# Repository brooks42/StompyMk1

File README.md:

# StompyMk1
A small quadruped robot made of 9g servos and hope.

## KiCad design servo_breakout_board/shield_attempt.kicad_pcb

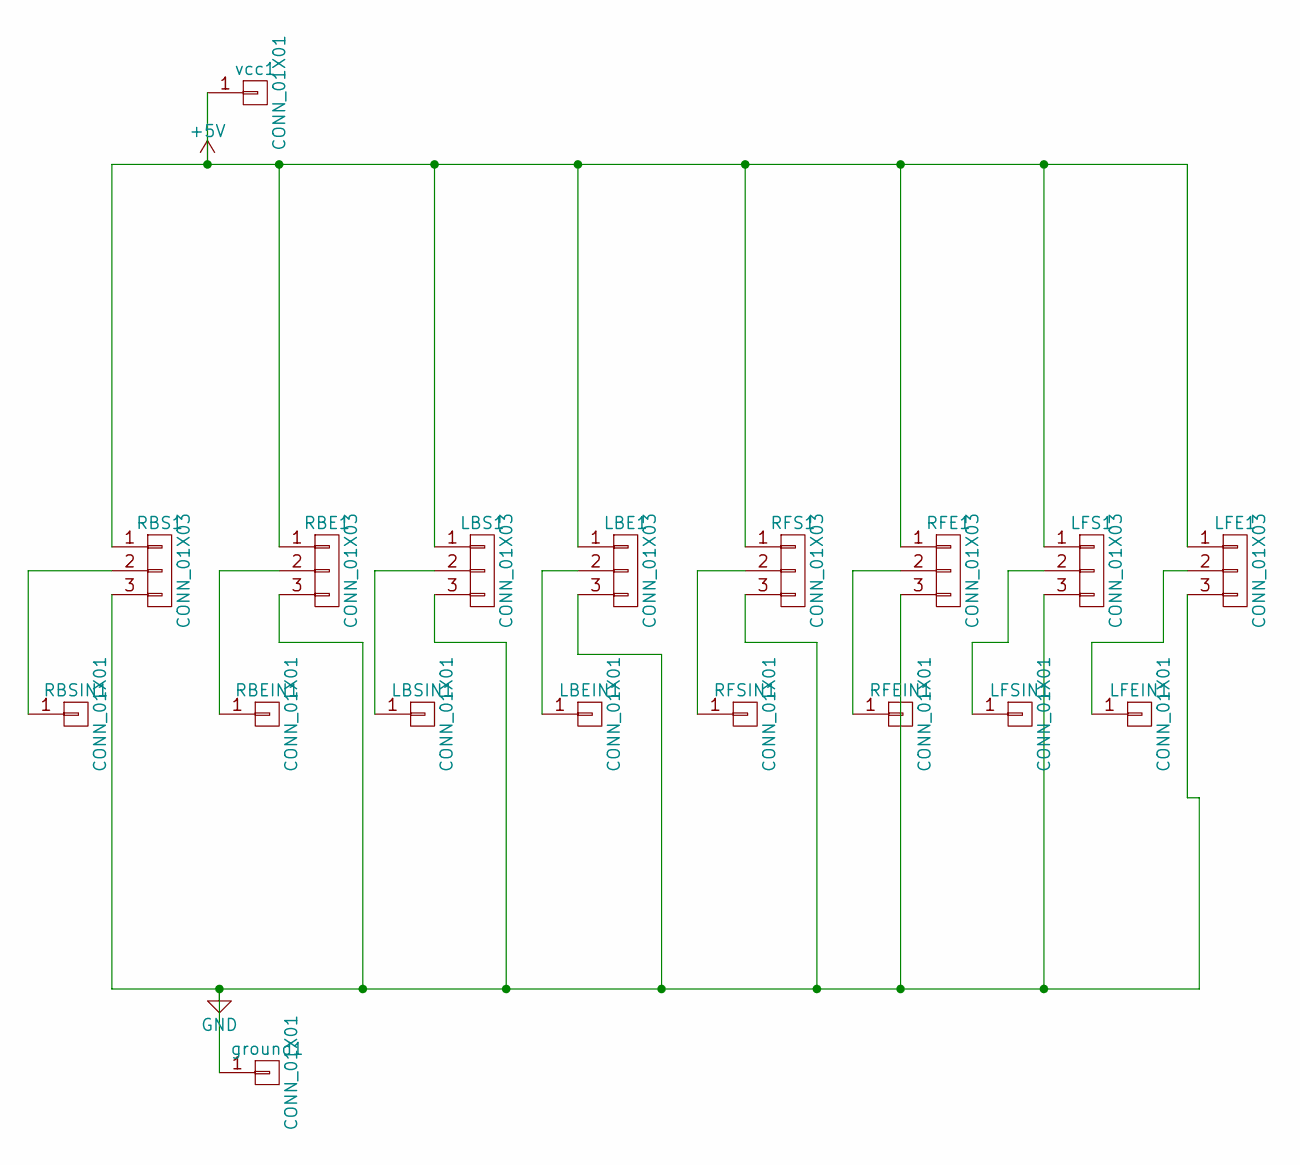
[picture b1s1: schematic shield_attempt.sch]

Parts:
LBE1: CONN_01X03; Pin_Header_Straight_1x03
LBEIN1: CONN_01X01; Pin_Header_Straight_1x01
LBS1: CONN_01X03; Pin_Header_Straight_1x03
LBSIN1: CONN_01X01; Pin_Header_Straight_1x01
LFE1: CONN_01X03; Pin_Header_Straight_1x03
LFEIN1: CONN_01X01; Pin_Header_Straight_1x01
LFS1: CONN_01X03; Pin_Header_Straight_1x03
LFSIN1: CONN_01X01; Pin_Header_Straight_1x01
RBE1: CONN_01X03; Pin_Header_Straight_1x03
RBEIN1: CONN_01X01; Pin_Header_Straight_1x01
RBS1: CONN_01X03; Pin_Header_Straight_1x03
RBSIN1: CONN_01X01; Pin_Header_Straight_1x01
RFE1: CONN_01X03; Pin_Header_Straight_1x03
RFEIN1: CONN_01X01; Pin_Header_Straight_1x01
RFS1: CONN_01X03; Pin_Header_Straight_1x03
RFSIN1: CONN_01X01; Pin_Header_Straight_1x01
ground1: CONN_01X01; Pin_Header_Straight_1x01
vcc1: CONN_01X01; Pin_Header_Straight_1x01

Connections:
+5V: LBE1.1, LBS1.1, LFE1.1, LFS1.1, RBE1.1, RBS1.1, RFE1.1, RFS1.1, vcc1.1
GND: LBE1.3, LBS1.3, LFE1.3, LFS1.3, RBE1.3, RBS1.3, RFE1.3, RFS1.3, ground1.1
unnamed: LBE1.2, LBEIN1.1
unnamed: LBS1.2, LBSIN1.1
unnamed: LFE1.2, LFEIN1.1
unnamed: LFS1.2, LFSIN1.1
unnamed: RBE1.2, RBEIN1.1
unnamed: RBS1.2, RBSIN1.1
unnamed: RFE1.2, RFEIN1.1
unnamed: RFS1.2, RFSIN1.1

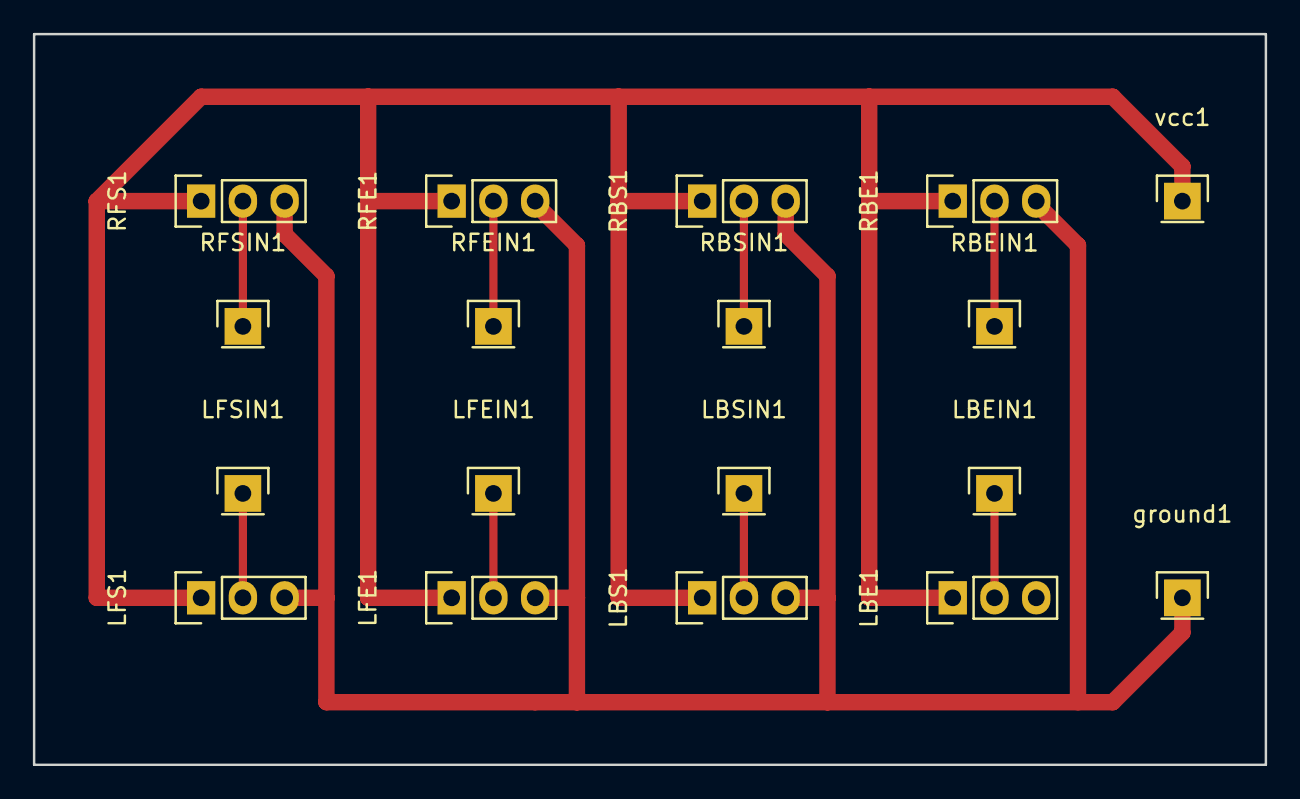
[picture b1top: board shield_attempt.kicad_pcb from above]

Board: 2 copper layers, 74.9 x 44.5 mm, 18 parts (0 on the bottom side), 10 nets.

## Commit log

2016-08-20 Initial commit of Stompy Mk1
2016-08-20 Update the brace mount to be thicker, and the body bottom piece to support direct servo arm horn mounting.
2016-08-20 Update the bottom to mount arm orns more snuggly
2016-08-20 Remove the old body_1 file
2016-08-20 Update the top to work with the new servo braces
2016-08-29 Update the Stompy Top to fit a thicker servo mount
2016-11-05 Add the servo breakout board for Stompy. Also finally doing this on a mac so I added the DS_Store to the gitignore
2016-11-07 Initial commit of some source for the beginning of StompyOS
2016-11-07 Add a single maintenant routine and a couple of IK header fields
2016-11-14 Add a copper fill to the board
2016-11-15 Second attempt at the main board
2017-01-09 Add the Headlight object definition.
2017-01-19 Add the new kinematics header for later, when Gatefinder is finished
